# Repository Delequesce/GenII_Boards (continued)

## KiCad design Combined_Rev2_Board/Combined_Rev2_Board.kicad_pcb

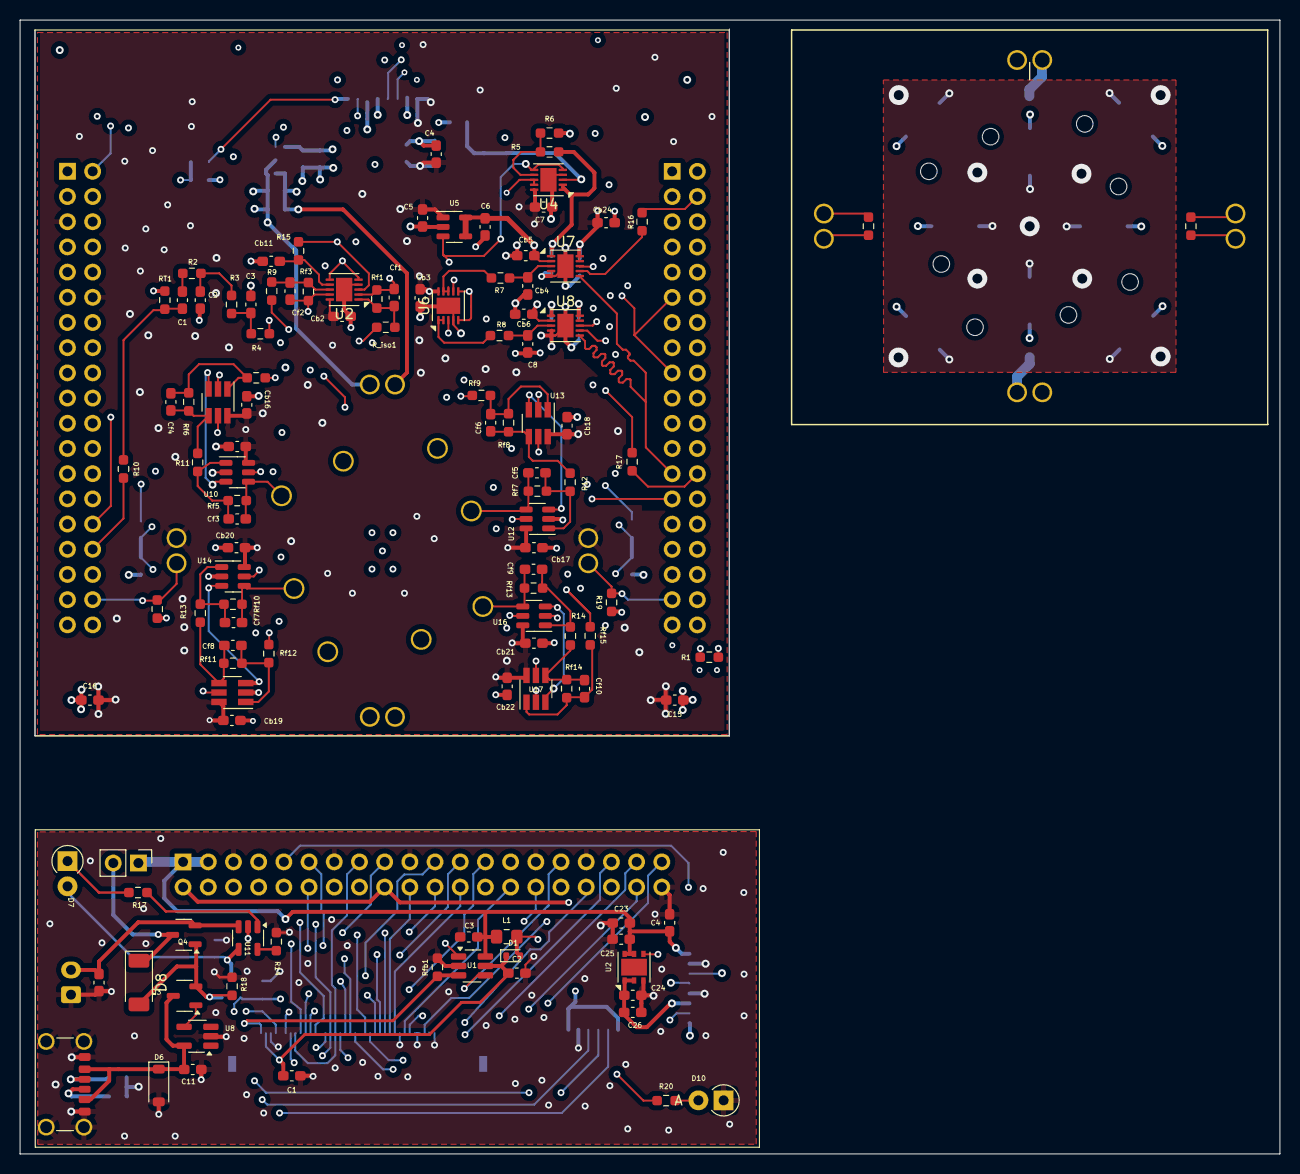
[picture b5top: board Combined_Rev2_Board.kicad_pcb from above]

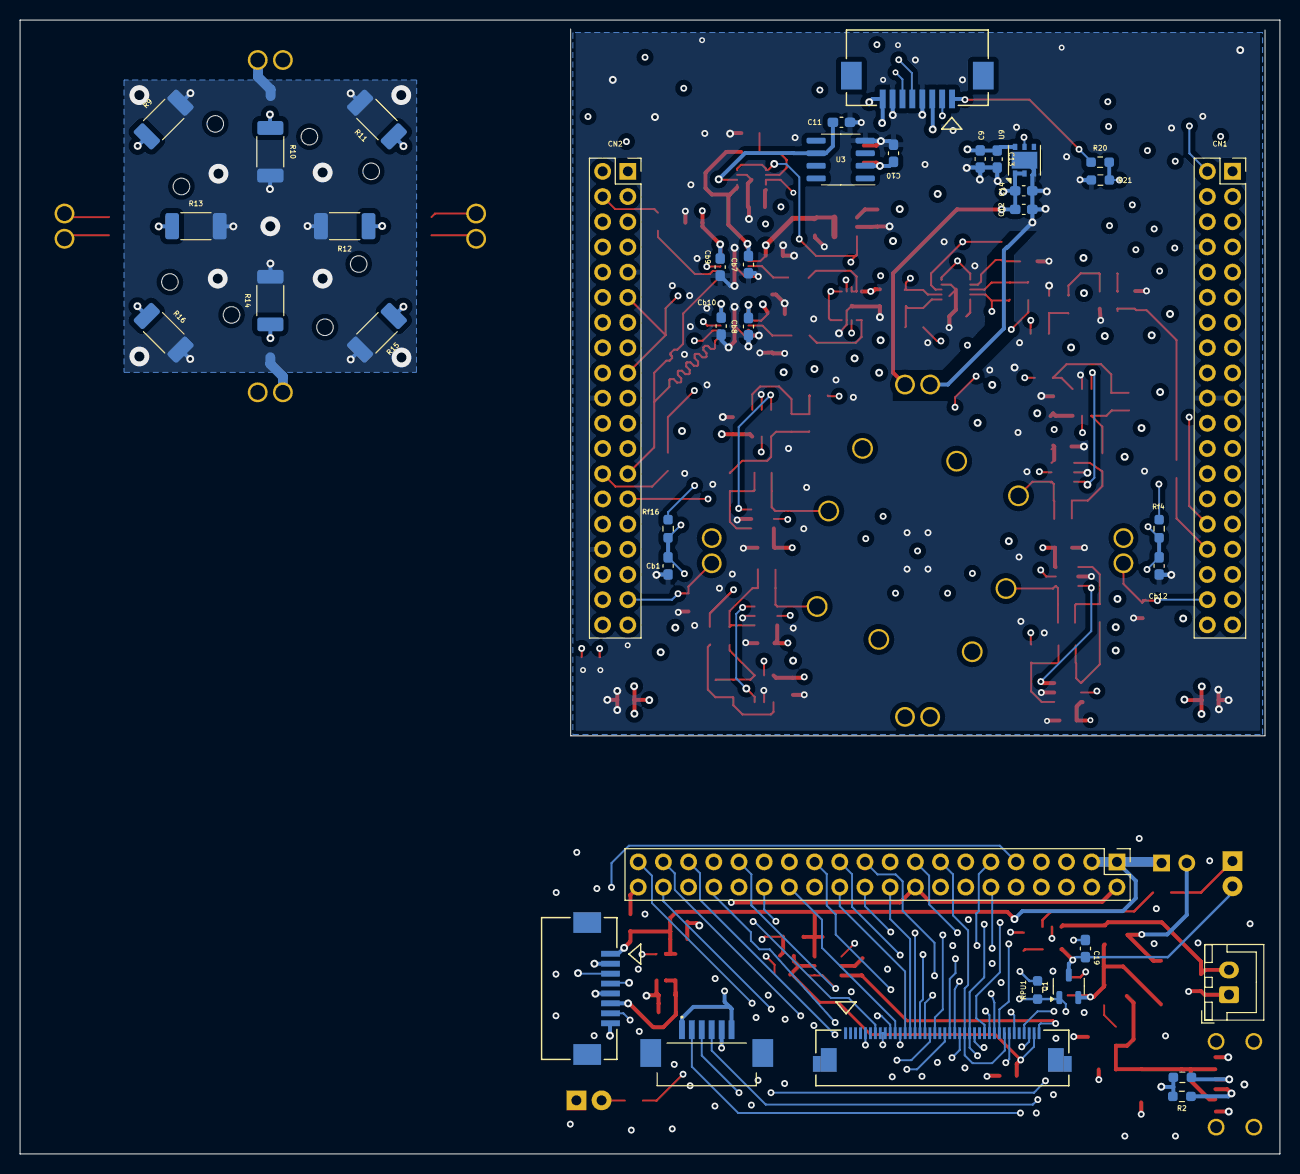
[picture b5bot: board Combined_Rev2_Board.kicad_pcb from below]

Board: 4 copper layers, 127.0 x 114.3 mm, 178 parts (39 on the bottom side), 117 nets.

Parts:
C1, C2, C3, C4, C7, C11#2: 1uF; C_0603_1608Metric_Pad1.08x0.95mm_HandSolder
C1#2: 100p; C_0603_1608Metric_Pad1.08x0.95mm_HandSolder
C2#2, C3#2: 47p; C_0603_1608Metric_Pad1.08x0.95mm_HandSolder
C4#2, C15, C16: 22u; C_0603_1608Metric_Pad1.08x0.95mm_HandSolder
C5, C6: 10uF; C_0603_1608Metric_Pad1.08x0.95mm_HandSolder
C8: 220p; C_0603_1608Metric_Pad1.08x0.95mm_HandSolder
C9, C12, C23, C24: 1uF/XR5; C_0603_1608Metric_Pad1.08x0.95mm_HandSolder
C10: 22uF; C_0603_1608Metric_Pad1.08x0.95mm_HandSolder
C11: 0.1u; C_0603_1608Metric_Pad1.08x0.95mm_HandSolder
C13, C14, C25, C26: 100n; C_0603_1608Metric_Pad1.08x0.95mm_HandSolder
C19, C20: 10u; C_0603_1608Metric_Pad1.08x0.95mm_HandSolder
CN1: USB_C_Receptacle_PowerOnly_6P; USB_C_Receptacle_GCT_USB4125-xx-x_6P_TopMnt_Horizontal
CN1#2, CN2: Conn_02x19_Odd_Even; PinSocket_2x19_P2.54mm_Vertical
CN2#2: B2B-XH-A; JST_XH_B2B-XH-A_1x02_P2.50mm_Vertical
CN3: 522070860; CON_522070860_MOL
CN3#2: Molex FPC 541044031; CON_541044031_MOL
CN4, CN5, CN6, CN7: Conn_01x02_Pin; Samtec_Pin_Socket_SS_102_G_2
CN4#2: Molex FPC 52271-0679; MOLEX_52271-0679
CN5#2: Conn_02x20_Odd_Even; PinHeader_2x20_P2.54mm_Vertical
Cb1, Cb7, Cb8, Cb12: 10u; C_0603_1608Metric_Pad1.08x0.95mm_HandSolder
Cb2, Cb3, Cb5, Cb6, Cb9, Cb10, Cb15, Cb16, Cb17, Cb18, Cb19, Cb20, Cb21, Cb22, Cb24: 0.1u; C_0603_1608Metric_Pad1.08x0.95mm_HandSolder
Cb4: 220p; C_0603_1608Metric_Pad1.08x0.95mm_HandSolder
Cb11: 1u; C_0603_1608Metric_Pad1.08x0.95mm_HandSolder
Cf1: 27p; C_0603_1608Metric_Pad1.08x0.95mm_HandSolder
Cf2, Cf4, Cf6, Cf8, Cf10: 1p; C_0603_1608Metric_Pad1.08x0.95mm_HandSolder
Cf3, Cf5, Cf7, Cf9: 200p; C_0603_1608Metric_Pad1.08x0.95mm_HandSolder
D1: D_Schottky; D_SOD-523
D6: NC; D_SOD-123
D7, D10: LED; D_T-1_P2.54mm_Vertical_AnodeUp
D8: PMEG3030EP,115; D_SOD-128
H9, H10, H11, H12, H13, H14, H15, H16: PogoPinClearanceHole; PogoClearanceHole
J1, J2, J3, J4, J5, J6#2, J7, J8: MIllMaxSpringConnector; MillMax_0914-2
J1#2, J5#2, J6, J7#2: Conn_01x02_Pin; Samtec_Pin_Socket_SS_102_G_2
J1#3: 522070860; CON_522070860_MOL
L1: 22uH; L_0805_2012Metric_Pad1.15x1.40mm_HandSolder
Q1: SI2347DS-TI-GE3CT; SOT-23-3
Q3: DMG3406L-7; SOT-23-3
Q4: SSM3J358R; SOT-23-3
R1, R10, R16, R17#2: 33; R_0603_1608Metric_Pad0.98x0.95mm_HandSolder
R1#2, R2#2: 5.1k; R_0603_1608Metric_Pad0.98x0.95mm_HandSolder
R2, R3, R5, R6, R18#2, R20#2, R21: 10k; R_0603_1608Metric_Pad0.98x0.95mm_HandSolder
R4, R9, R11, R12, R13, R14, R15, R17, R18, R19, R20: 1k; R_0603_1608Metric_Pad0.98x0.95mm_HandSolder
R7, R8: 100; R_0603_1608Metric_Pad0.98x0.95mm_HandSolder
R9#2, R10#2, R11#2, R12#2, R13#2, R14#3, R15#2, R16#2: 50; R_2010_5025Metric_Pad1.40x2.65mm_HandSolder
R14#2: 2k; R_0603_1608Metric_Pad0.98x0.95mm_HandSolder
RPU1: 5k; R_0603_1608Metric_Pad0.98x0.95mm_HandSolder
RT1: NC; R_0603_1608Metric_Pad0.98x0.95mm_HandSolder
R_iso1: 10; R_0603_1608Metric_Pad0.98x0.95mm_HandSolder
Rf1: 1.5k; R_0603_1608Metric_Pad0.98x0.95mm_HandSolder
Rf3, Rf6, Rf8, Rf11, Rf14: 39k; R_0603_1608Metric_Pad0.98x0.95mm_HandSolder
Rf4, Rf16: 100; R_0603_1608Metric_Pad0.98x0.95mm_HandSolder
Rf5, Rf7, Rf10, Rf13: 50; R_0603_1608Metric_Pad0.98x0.95mm_HandSolder
Rf9, Rf12, Rf15: 10; R_0603_1608Metric_Pad0.98x0.95mm_HandSolder
Rfb1: 6.25; R_0603_1608Metric_Pad0.98x0.95mm_HandSolder
Riso1: 10; R_0603_1608Metric_Pad0.98x0.95mm_HandSolder
SW2: Rocker Switch SPST; PinHeader_1x02_P2.54mm_Vertical
TH5, TH7: Thermistor_NTC; R_0603_1608Metric_Pad0.98x0.95mm_HandSolder
U1: AP5725WG-7; SOT-23-6_Handsoldering
U2: LD39200; DFN-6-1EP_3x3mm_P0.95mm_EP1.7x2.6mm
U2#2, U4, U6: ADA4807-2ACP; LFCSP-WD-10-1EP_3x3mm_P0.5mm_EP1.64x2.38mm
U3: ADR4530; SOIC-8_3.9x4.9mm_P1.27mm
U5: ADP7118-1.8; TSOT-23-5
U7, U8#2: AD4002_LFSCP-10; LFCSP-WD-10-1EP_3x3mm_P0.5mm_EP1.64x2.38mm
U8: TPS2400; SOT-23-5_HandSoldering
U9: LD39200_Fixed; DFN-6-1EP_3x3mm_P0.95mm_EP1.7x2.6mm
U10, U12, U14, U16: LTC6252; TSOT-23-6
U11: MCP73831-2-OT; SOT-23-5
U11#2, U13, U15, U17: ADA4807-1; SOT-23-6_Handsoldering

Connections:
/3V3_Main: C24.1, C26.1, J1#3.6, U2.1 (Vout), U2.2 (ADJ/SENSE)
/3V3_Pi: CN3#2.37, CN4#2.1, CN4#2.6, CN5#2.2, CN5#2.18
/ABBCore_Alt/TIA_1/V_MID: Cb12.2, Rf4.2, U10.3 (+), U11#2.3 (+), U14.3 (+), U15.3 (+)
/ABBCore_Alt/TIA_2/V_MID: Cb1.2, Rf16.2, U12.3 (+), U13.3 (+), U16.3 (+), U17.3 (+)
/ABBCore_Alt/V_Drive: J3.1, J4.1, J7.1, J8.1, R9.2, R_iso1.2
/ABBCore_Alt/V_Exc: Cf2.2, Rf3.2, U2#2.9, U6.7 (+)
/ABBCore_Alt/V_Resp: Rf9.2, Rf12.2, Rf15.2, Riso1.2, U6.3 (+)
/B1: CN3#2.19, CN5#2.30
/B2: CN3#2.18, CN5#2.32
/B3: CN3#2.17, CN5#2.25
/B4: CN3#2.16, CN5#2.23
/B5: CN3#2.15, CN5#2.22
/B6: CN3#2.14, CN5#2.20
/B7: CN3#2.13, CN5#2.24
/CLK: CN3#2.11, CN5#2.28
/DE: CN3#2.7, CN5#2.27
/DISP: CN3#2.10, CN5#2.37
/G1: CN3#2.27, CN5#2.34
/G2: CN3#2.26, CN3#2.34, CN5#2.16
/G3: CN3#2.25, CN3#2.33, CN5#2.15
/G4: CN3#2.24, CN5#2.35
/G5: CN3#2.23, CN5#2.12
/G6: CN3#2.22, CN5#2.11
/G7: CN3#2.21, CN5#2.36
/Heater_Interface/Heater+: C12.1, C14.1, CN7.2, U9.1 (Vout), U9.2 (ADJ/SENSE)
/LED+: C1.2, C2.1, CN3#2.39, D1.1 (K), U1.5 (OVP)
/LED-: CN3#2.40, Rfb1.2, U1.3 (FB)
/MCU Connections/PA1: CN1#2.32, R10.1
/MCU Connections/PB4: CN2.4, R16.2
/MCU Connections/PB6: CN2.34, R1.1
/MCU Connections/PB15: CN2.26, R17#2.1
/MCU Connections/PC1: CN1#2.30, R20#2.2, R21.1
/PWM_EN: CN5#2.31, U1.4 (EN)
/Power_Management_Minimal/5V_USB: D8.2 (A), Q1.2 (S), Q3.2 (S), Q4.1 (G), R18#2.1
/Power_Management_Minimal/VBus: C11.1, CN1.A9 (VBUS), CN1.B9 (VBUS), D6.1 (K), Q3.3 (D), U8.5 (Vin)
/R1: CN3#2.35, CN5#2.39
/R4: CN3#2.32, CN5#2.17
/R5: CN3#2.31, CN5#2.21
/R6: CN3#2.30, CN5#2.38
/R7: CN3#2.29, CN5#2.14
/SCL: CN4#2.4, CN5#2.6
/SDA: CN4#2.3, CN5#2.4
/UART_RX: CN5#2.9, J1#3.4
/UART_TX: CN5#2.7, J1#3.3
/USB_VCC1: CN1.A5 (CC1), R1#2.2
/USB_VCC2: CN1.B5 (CC2), R2#2.2
/V_Batt: C20.1, CN2#2.2, J1#3.8, Q4.2 (S), U11.3 (V_{BAT})
/Vcc: C3.1, C4#2.1, C23.2, C25.1, CN5#2.1, CN5#2.3, J1#3.1, L1.1, SW2.1 (A), U1.6 (VIN), U2.5 (EN), U2.6 (Vin)
/~CHARGE_EN: J1#3.7, Q1.1 (G), RPU1.1
/~INT: CN4#2.2, CN5#2.8
ADC_VREF: Cb7.2, Cb8.2, R5.1, U4.1, U4.2 (-), U7.1 (REF), U8#2.1 (REF)
CCOut_1: Cf3.1, J6#2.1, Rf5.1, U10.4 (-)
CCOut_2: Cf5.1, J5.1, Rf7.1, U12.4 (-)
CCOut_3: Cf7.1, J2.1, Rf10.1, U14.4 (-)
CCOut_4: Cf9.1, J1.1, Rf13.1, U16.4 (-)
CNV: CN2.25, U7.6 (CNV), U8#2.6 (CNV)
DataOut1: R17#2.2, U8#2.7 (SDO)
Dataout0: R16.1, U7.7 (SDO)
GND: C1.1, C2.2, C2#2.2, C3.2, C3#2.2, C4.2, C4#2.2, C5.2, C6.2, C7.2, C8.1, C9.1, C10.1, C11.2, C11#2.1, C12.2, C13.2, C14.2, C15.1, C16.1, C19.1, C20.2, C23.1, C24.2, C25.2, C26.2, CN1.A12 (GND), CN1.B12 (GND), CN1.S1 (SHIELD), CN1#2.8, CN1#2.19, CN1#2.20, CN2.9, CN2.20, CN2.32, CN2#2.1, CN3.4, CN3.7, CN3#2.5, CN3#2.8, CN3#2.9, CN3#2.12, CN3#2.38, CN4#2.5, CN5#2.5, CN5#2.10, CN5#2.13, CN5#2.19, CN5#2.26, CN5#2.29, CN5#2.33, CN5#2.40, CN7.1, Cb1.1, Cb2.1, Cb3.2, Cb4.1, Cb5.2, Cb6.2, Cb7.1, Cb8.1, Cb9.1, Cb10.1, Cb11.1, Cb12.1, Cb15.1, Cb16.1, Cb17.1, Cb18.1, Cb19.1, Cb20.1, Cb21.1, Cb22.1, Cb24.1, D6.2 (A), D10.1 (K), J1#3.2, J1#3.5, R1#2.1, R2#2.1, R6.2, R14#2.1, R18.1, R18#2.2, R19.1, R21.2, RPU1.2, RT1.1, Rfb1.1, U1.2 (GND), U2.3 (GND), U2#2.4 (V-), U2#2.11 (EPAD), U3.4 (GND), U4.4 (V-), U4.11 (EPAD), U5.2 (GND), U6.4 (V-), U6.11 (EPAD), U7.4 (IN-), U7.5 (GND), U7.11 (Pad), U8.2 (GND), U8#2.4 (IN-), U8#2.5 (GND), U8#2.11 (Pad), U9.3 (GND), U10.2 (V-), U11.2 (V_{SS}), U11#2.2 (V-), U12.2 (V-), U13.2 (V-), U14.2 (V-), U15.2 (V-), U16.2 (V-), U17.2 (V-)
Heater_EN: CN1#2.1, U9.5 (EN)
MCU_SCK: CN2.11, CN2.17, U7.8 (SCK), U8#2.8 (SCK)
unnamed: C1#2.1, R2.1
unnamed: C2#2.1, R2.2, R3.1
unnamed: C3#2.1, R3.2, R4.1
unnamed: Cf1.1, R_iso1.1, Rf1.1, U2#2.1
unnamed: Cf3.2, R11.2, Rf5.2, U10.1
unnamed: Cf4.2, Rf6.2, Riso1.1, U11#2.1
unnamed: Cf5.2, R12.2, Rf7.2, U12.1
unnamed: Cf6.2, Rf8.2, Rf9.1, U13.1
unnamed: Cf7.2, R13.2, Rf10.2, U14.1
unnamed: Cf8.2, Rf11.2, Rf12.1, U15.1
unnamed: Cf9.2, R14.2, Rf13.2, U16.1
unnamed: Cf10.2, Rf14.2, Rf15.1, U17.1
unnamed: D1.2 (A), L1.2, U1.1 (SW)
unnamed: C19.2, D7.2 (A), Q1.3 (D), U11.4 (V_{DD})
unnamed: D7.1 (K), R17.2
unnamed: D8.1 (K), Q4.3 (D), SW2.2 (B)
unnamed: D10.2 (A), R20.2
unnamed: J1#2.2, J5#2.2, R9#2.1, R10#2.1, R11#2.1, R12#2.1, R13#2.1, R14#3.1, R15#2.1, R16#2.1
unnamed: J6.1, TH7.1
unnamed: J6.2, TH7.2
unnamed: J7#2.1, TH5.1
unnamed: J7#2.2, TH5.2
unnamed: Q3.1 (G), U8.4 (Gate)
unnamed: R20.1, U2.4 (PWRGD)
unnamed: Cf1.2, R4.2, Rf1.2, U2#2.2 (-)
unnamed: Cb11.2, R15.2, U2#2.7 (+)
unnamed: Cf2.1, R9.1, Rf3.1, U2#2.8 (-)
unnamed: C11#2.2, U3.6 (OUT), U4.3 (+)
unnamed: R5.2, R6.1, U4.7 (+)
unnamed: R8.2, U6.1, U6.2 (-)
unnamed: R7.2, U6.8 (-), U6.9
unnamed: Cb4.2, R7.1, U7.3 (IN+)
unnamed: C8.2, R8.1, U8#2.3 (IN+)
unnamed: Cf4.1, R11.1, Rf6.1, U11#2.4 (-)
unnamed: R14#2.2, U11.5 (PROG)
unnamed: R17.1, U11.1 (STAT)
unnamed: Cf6.1, R12.1, Rf8.1, U13.4 (-)
unnamed: Cf8.1, R13.1, Rf11.1, U15.4 (-)
unnamed: Cf10.1, R14.1, Rf14.1, U17.4 (-)
UART_RX: CN2.6, CN3.6
UART_TX: CN3.5, R1.2
V_Batt: CN3.1, R20#2.1
V_MID: R15.1, Rf4.1, Rf16.1, U2#2.3 (+), U4.8 (-), U4.9
V_SIG: C1#2.2, R10.2, RT1.2
Vcc: C9.2, C13.1, CN3.3, U9.6 (Vin)
Vdd_ADC: C6.1, Cb5.1, Cb6.1, U5.4 (SENSE/ADJ), U5.5 (VOUT), U7.2 (Vdd), U8#2.2 (Vdd)
Vdd_Heater_2: J1#2.1, J5#2.1, R9#2.2, R10#2.2, R11#2.2, R12#2.2, R13#2.2, R14#3.2, R15#2.2, R16#2.2
Vdd_Main: C4.1, C5.1, C7.1, C10.2, C15.2, C16.2, CN1#2.5, CN1#2.12, CN3.8, CN4.1, CN5.1, Cb2.2, Cb3.1, Cb9.2, Cb10.2, Cb15.2, Cb16.2, Cb17.2, Cb18.2, Cb19.2, Cb20.2, Cb21.2, Cb22.2, Cb24.2, U2#2.10 (V+), U3.2 (IN), U4.10 (V+), U5.1 (VIN), U6.10 (V+), U7.9 (SDI), U7.10 (VIO), U8#2.9 (SDI), U8#2.10 (VIO), U10.6 (V+), U11#2.6 (V+), U12.6 (V+), U13.6 (V+), U14.6 (V+), U15.6 (V+), U16.6 (V+), U17.6 (V+)
Vth_1: CN1#2.36, CN4.2, R18.2
Vth_2: CN2.35, CN5.2, R19.2
~ADC1_SHDN: CN2.1, U2#2.5 (~DISABLE1), U2#2.6 (~DISABLE2), U4.5 (~DISABLE1), U4.6 (~DISABLE2), U5.3 (EN), U6.5 (~DISABLE1), U6.6 (~DISABLE2)
~CHARGE_EN: CN1#2.2, CN3.2
~TIA1_SHDN: CN1#2.28, U10.5 (~SHDN), U11#2.5 (~DISABLE)
~TIA2_SHDN: CN2.27, U12.5 (~SHDN), U13.5 (~DISABLE)
~TIA3_SHDN: CN1#2.34, U14.5 (~SHDN), U15.5 (~DISABLE)
~TIA4_SHDN: CN2.33, U16.5 (~SHDN), U17.5 (~DISABLE)

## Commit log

2024-09-10 Initial File Commit
2024-09-10 Heater and Footprint Initial Commit
2024-09-10 Checking if Branch Updates Work
2024-09-13 Small Updates
2024-09-16 Finished USB-C Power Board Design
2024-09-20 Pre-Local Repo Commit
2024-10-02 Raspberry Pi Board Added
2024-10-03 First draft layout of power pi board
2024-10-05 Completed (unflipped) board
2024-10-06 Partial Update
2024-10-07 Finalized Ras_Pi Power Board
2024-10-07 Small change to Raspi Board
2024-10-08 Finished Measurement Board Update Minus Heater Board Connections
2024-10-11 Boards nearly finalized
2024-10-25 Nearly Finalized Boards
2024-10-28 Final commit before order
2024-10-28 Following Board Resubmit
2025-01-30 Final Rev 2 Commit
2025-01-30 gitignore modification
2025-01-30 Added Readme
2025-01-31 First Pass Schematic Fixes for Power Management Board
2025-02-03 Finished Rasp Board PCB Routing
2025-02-03 Finished Measurement Board Fixes Schematic and PCB
2025-02-04 Updated Measurement Board with new 3V Reference
2025-02-05 Final Edit Before Check and Combine
2025-02-10 Final Rev3 Commit Post Submission
